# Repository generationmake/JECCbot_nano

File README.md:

# JECCbot_nano
Small Open Source robotic platform

## PCB

### Top

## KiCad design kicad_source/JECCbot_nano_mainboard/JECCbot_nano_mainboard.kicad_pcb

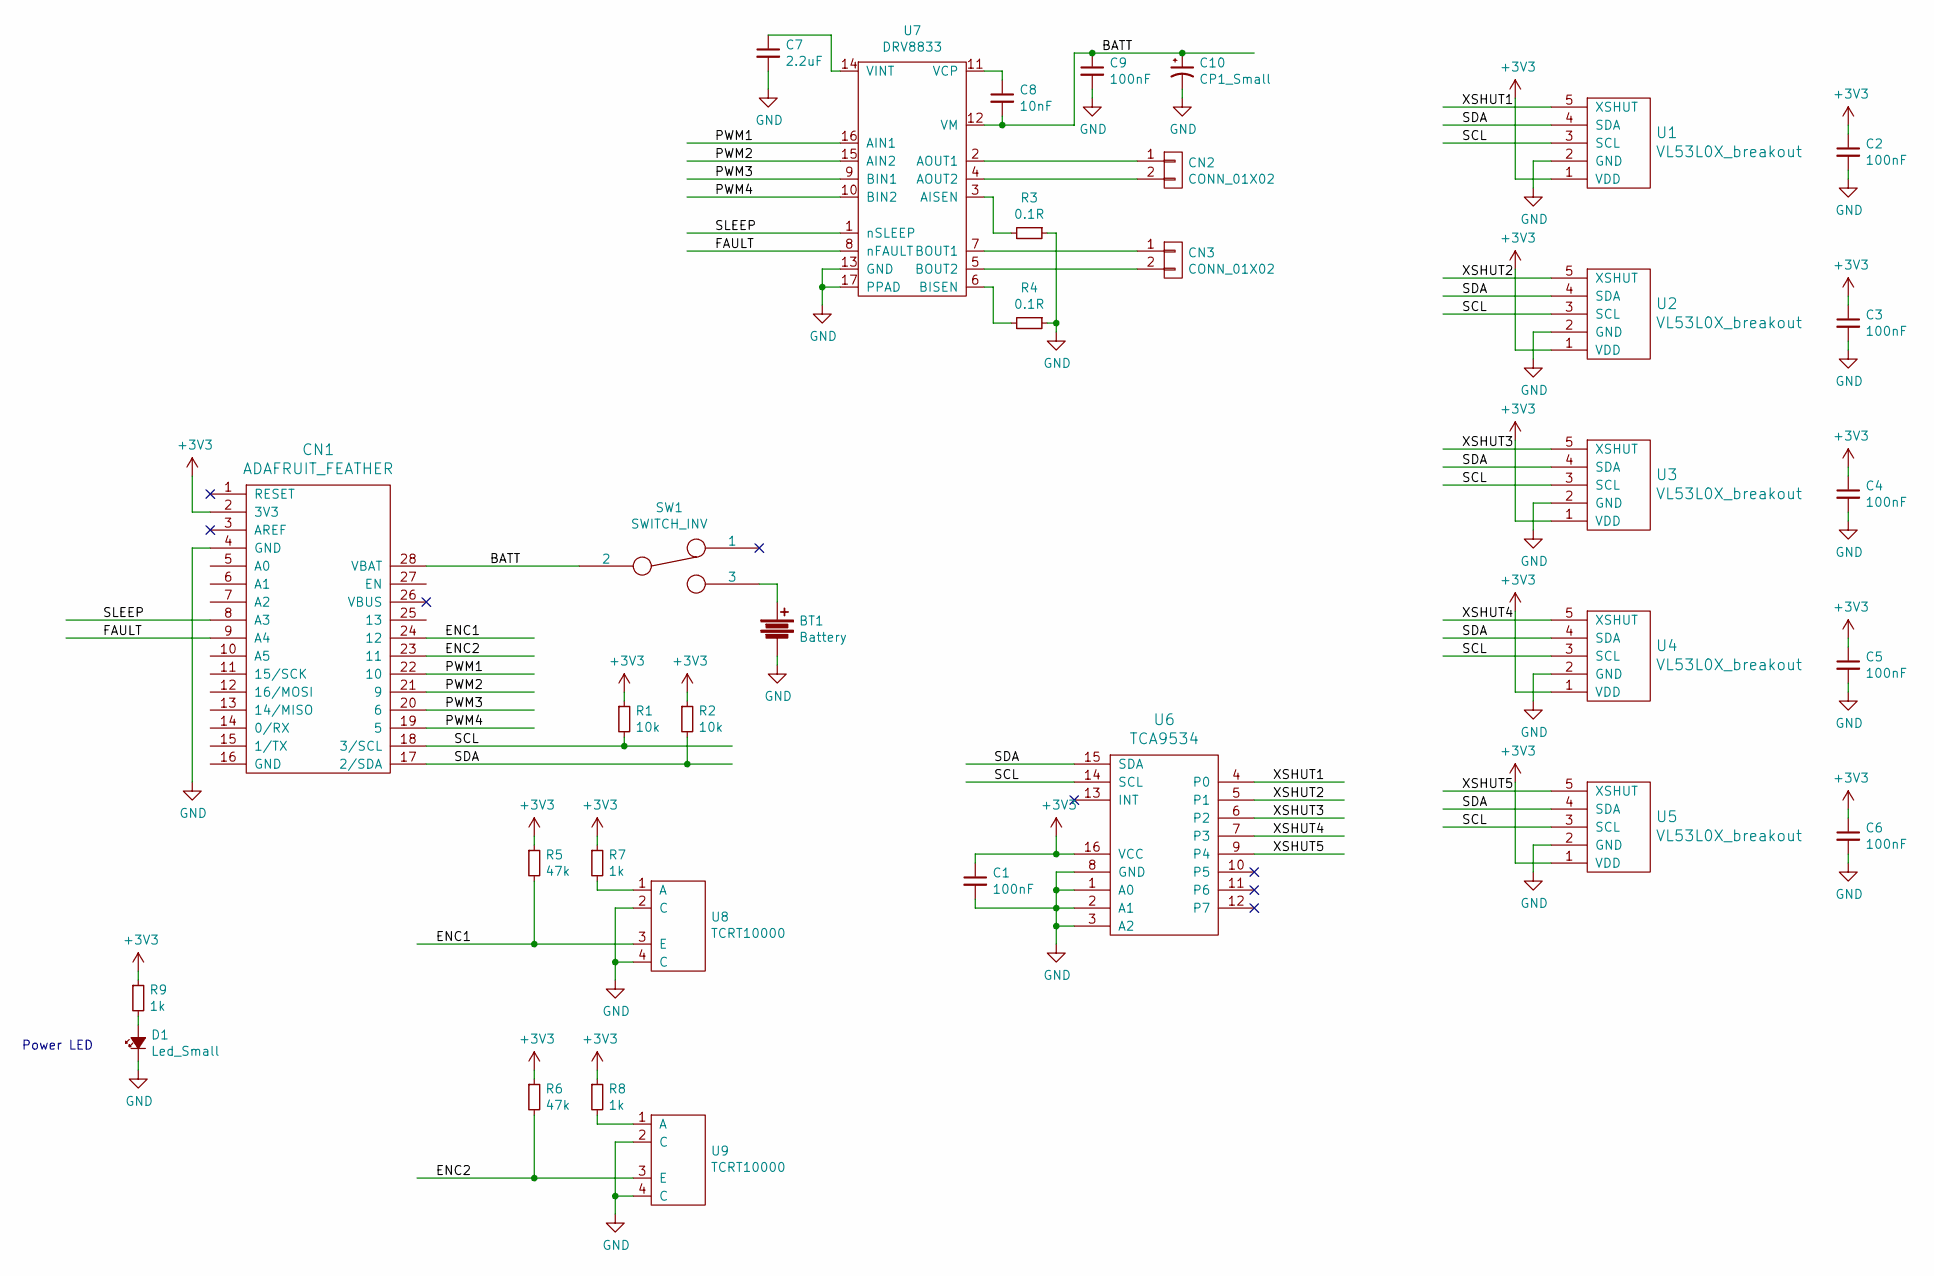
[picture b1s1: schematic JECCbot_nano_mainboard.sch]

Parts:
BT1: Battery; KEYSTONE_1043
C1, C2, C3, C4, C5, C6, C9: 100nF; C_0603
C7: 2.2uF; C_0603
C8: 10nF; C_0603
C10: CP1_Small; TantalC_SizeD_EIA-7343_Wave
CN1: ADAFRUIT_FEATHER; ADAFRUIT_FEATHER_HOLES
CN2, CN3: CONN_01X02; Pin_Header_Straight_1x02
D1: Led_Small; LED_0603
R1, R2: 10k; R_0603
R3, R4: 0.1R; R_0805
R5, R6: 47k; R_0603
R7, R8, R9: 1k; R_0603
SW1: SWITCH_INV; Würth_WS-SLTV
U1, U2, U3, U4, U5: VL53L0X_breakout
U6: TCA9534; SOIC-16_7.5x10.3mm_Pitch1.27mm
U7: DRV8833; TSSOP-16-1EP_4.4x5mm_Pitch0.65mm
U8, U9: TCRT10000; TCRT1000

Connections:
+3V3: C1.1, C2.1, C3.1, C4.1, C5.1, C6.1, CN1.2 (3V3), R1.1, R2.1, R5.1, R6.1, R7.1, R8.1, R9.1, U1.1 (VDD), U2.1 (VDD), U3.1 (VDD), U4.1 (VDD), U5.1 (VDD), U6.16 (VCC)
/BATT: C8.2, C9.1, C10.1, CN1.28 (VBAT), SW1.2, U7.12 (VM)
/ENC1: CN1.24 (12), R5.2, U8.3 (E)
/ENC2: CN1.23 (11), R6.2, U9.3 (E)
/FAULT: CN1.9 (A4), U7.8 (nFAULT)
/PWM1: CN1.22 (10), U7.16 (AIN1)
/PWM2: CN1.21 (9), U7.15 (AIN2)
/PWM3: CN1.20 (6), U7.9 (BIN1)
/PWM4: CN1.19 (5), U7.10 (BIN2)
/SCL: CN1.18 (3/SCL), R1.2, U1.3 (SCL), U2.3 (SCL), U3.3 (SCL), U4.3 (SCL), U5.3 (SCL), U6.14 (SCL)
/SDA: CN1.17 (2/SDA), R2.2, U1.4 (SDA), U2.4 (SDA), U3.4 (SDA), U4.4 (SDA), U5.4 (SDA), U6.15 (SDA)
/SLEEP: CN1.8 (A3), U7.1 (nSLEEP)
/XSHUT1: U1.5 (XSHUT), U6.4 (P0)
/XSHUT2: U2.5 (XSHUT), U6.5 (P1)
/XSHUT3: U3.5 (XSHUT), U6.6 (P2)
/XSHUT4: U4.5 (XSHUT), U6.7 (P3)
/XSHUT5: U5.5 (XSHUT), U6.9 (P4)
GND: BT1.2, C1.2, C2.2, C3.2, C4.2, C5.2, C6.2, C7.2, C9.2, C10.2, CN1.4 (GND), D1.1 (K), R3.1, R4.1, U1.2 (GND), U2.2 (GND), U3.2 (GND), U4.2 (GND), U5.2 (GND), U6.1 (A0), U6.2 (A1), U6.3 (A2), U6.8 (GND), U7.13 (GND), U7.17 (PPAD), U8.2 (C), U8.4 (C), U9.2 (C), U9.4 (C)
unnamed: BT1.1, SW1.3
unnamed: C7.1, U7.14 (VINT)
unnamed: C8.1, U7.11 (VCP)
unnamed: CN2.1, U7.2 (AOUT1)
unnamed: CN2.2, U7.4 (AOUT2)
unnamed: CN3.1, U7.7 (BOUT1)
unnamed: CN3.2, U7.5 (BOUT2)
unnamed: D1.2 (A), R9.2
unnamed: R3.2, U7.3 (AISEN)
unnamed: R4.2, U7.6 (BISEN)
unnamed: R7.2, U8.1 (A)
unnamed: R8.2, U9.1 (A)

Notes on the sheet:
Power LED

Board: 2 copper layers, 34 parts (1 on the bottom side), 30 nets, no tracks yet.

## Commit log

2020-02-02 added kicad projects for VL53L0X breakout board and JECCbot nano mainboard
2020-02-02 moved motors 2 mm backwards to make space for bigger wheels and generated step file
2020-02-02 added images of pcb
2020-02-02 cropped images
2020-02-02 added freecad project for JECCbot nano
2020-02-02 updated CAD file of JECCbot, increased wheel size to 28 mm
2020-02-02 added rendering of JECCbot nano
